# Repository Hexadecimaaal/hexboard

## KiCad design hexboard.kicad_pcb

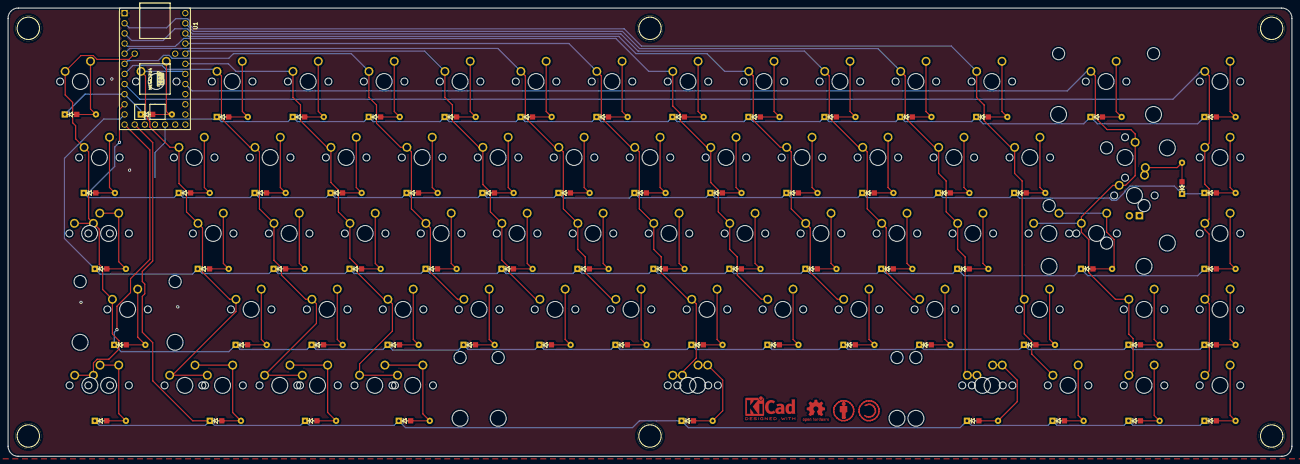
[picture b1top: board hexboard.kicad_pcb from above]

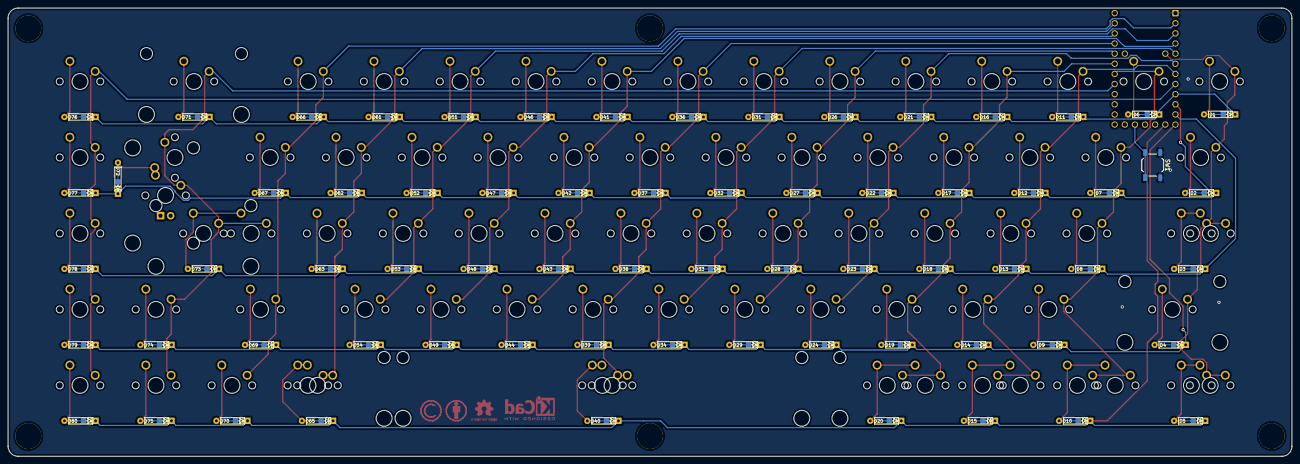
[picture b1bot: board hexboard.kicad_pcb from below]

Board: 2 copper layers, 321.9 x 112.4 mm, 151 parts (68 on the bottom side), 89 nets.

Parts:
D1, D2, D3, D4, D5, D6, D7, D8, D9, D10, D11, D12, D13, D14, D15, D16, D17, D18, D19, D20, D21, D22, D23, D24, D26, D27, D28, D29, D31, D32, D33, D34, D36, D37, D38, D39, D40, D41, D42, D43, D44, D46, D47, D48, D49, D51, D52, D53, D54, D61, D62, D63, D65, D66, D67, D69, D70, D71, D72, D73, D74, D75, D76, D77, D78, D79, D80: D_Small; Diode-hybrid-3pad
MX1, MX6, MX7, MX8, MX9, MX11, MX12, MX13, MX14, MX16, MX17, MX18, MX19, MX21, MX22, MX23, MX24, MX26, MX27, MX28, MX29, MX31, MX32, MX33, MX34, MX36, MX37, MX38, MX39, MX41, MX42, MX43, MX44, MX46, MX47, MX48, MX49, MX51, MX52, MX53, MX54, MX61, MX62, MX63, MX65ALT1, MX66, MX67, MX70, MX73ALT1, MX74, MX75, MX76, MX77, MX78, MX79, MX80: MX-NoLED; MXOnly-1U-NoLED
MX2: MX-NoLED; MXOnly-1.5U-NoLED
MX3, MX5, MX69: MX-NoLED; MXOnly-1.75U-NoLED
MX3ALT1, MX5ALT1, MX10, MX10ALT1, MX15, MX15ALT1, MX20, MX20ALT1, MX65: MX-NoLED; MXOnly-1.25U-NoLED
MX4, MX73: MX-NoLED; MXOnly-2.25U-NoLED
MX40: MX-NoLED; MXOnly-6.25U-NoLED
MX40ALT1: MX-NoLED; MXOnly-7U-NoLED
MX71: MX-NoLED; MXOnly-2U-NoLED
MX72: MX-NoLED; MXOnly-1.5U-Vertical-NoLED
MX72ALT1: MX-NoLED; MXOnly-ISO
SW1: SW_Push; SW_SPST_TL3342
U1: Teensy2.0_(C); Teensy2.0
U4, U4#2, U4#3, U4#4, U4#5, U4#6: HOLE; MountingHole

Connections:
/col1: MX1.1, MX2.1, MX3.1, MX3ALT1.1, MX4.1, MX5.1, MX5ALT1.1, U1.30
/col2: MX6.1, MX7.1, MX8.1, MX9.1, MX10.1, MX10ALT1.1, U1.23
/col3: MX11.1, MX12.1, MX13.1, MX14.1, MX15.1, MX15ALT1.1, U1.7
/col4: MX16.1, MX17.1, MX18.1, MX19.1, MX20.1, MX20ALT1.1, U1.24
/col5: MX21.1, MX22.1, MX23.1, MX24.1, U1.6
/col6: MX26.1, MX27.1, MX28.1, MX29.1, U1.25
/col7: MX31.1, MX32.1, MX33.1, MX34.1, U1.5
/col8: MX36.1, MX37.1, MX38.1, MX39.1, MX40.1, MX40ALT1.1, U1.26
/col9: MX41.1, MX42.1, MX43.1, MX44.1, U1.4
/col10: MX46.1, MX47.1, MX48.1, MX49.1, U1.27
/col11: MX51.1, MX52.1, MX53.1, MX54.1, U1.3
/col12: MX61.1, MX62.1, MX63.1, MX65.1, MX65ALT1.1, U1.28
/col13: MX66.1, MX67.1, MX69.1, MX70.1, U1.2
/col14: MX71.1, MX72.1, MX72ALT1.1, MX73.1, MX73ALT1.1, MX74.1, MX75.1, U1.22
/col15: MX76.1, MX77.1, MX78.1, MX79.1, MX80.1, U1.8
/row1: D1.1, D6.1, D11.1, D16.1, D21.1, D26.1, D31.1, D36.1, D41.1, D46.1, D51.1, D61.1, D66.1, D71.1, D76.1, U1.9
/row2: D2.1, D7.1, D12.1, D17.1, D22.1, D27.1, D32.1, D37.1, D42.1, D47.1, D52.1, D62.1, D67.1, D72.1, D77.1, U1.10
/row3: D3.1, D8.1, D13.1, D18.1, D23.1, D28.1, D33.1, D38.1, D43.1, D48.1, D53.1, D63.1, D73.1, D78.1, U1.11
/row4: D4.1, D9.1, D14.1, D19.1, D24.1, D29.1, D34.1, D39.1, D44.1, D49.1, D54.1, D69.1, D74.1, D79.1, U1.12
/row5: D5.1, D10.1, D15.1, D20.1, D40.1, D65.1, D70.1, D75.1, D80.1, U1.13
GND: SW1.1, U1.1
unnamed: D1.2, MX1.2
unnamed: D2.2, MX2.2
unnamed: D3.2, MX3.2, MX3ALT1.2
unnamed: D4.2, MX4.2
unnamed: D5.2, MX5.2, MX5ALT1.2
unnamed: D6.2, MX6.2
unnamed: D7.2, MX7.2
unnamed: D8.2, MX8.2
unnamed: D9.2, MX9.2
unnamed: D10.2, MX10.2, MX10ALT1.2
unnamed: D11.2, MX11.2
unnamed: D12.2, MX12.2
unnamed: D13.2, MX13.2
unnamed: D14.2, MX14.2
unnamed: D15.2, MX15.2, MX15ALT1.2
unnamed: D16.2, MX16.2
unnamed: D17.2, MX17.2
unnamed: D18.2, MX18.2
unnamed: D19.2, MX19.2
unnamed: D20.2, MX20.2, MX20ALT1.2
unnamed: D21.2, MX21.2
unnamed: D22.2, MX22.2
unnamed: D23.2, MX23.2
unnamed: D24.2, MX24.2
unnamed: D26.2, MX26.2
unnamed: D27.2, MX27.2
unnamed: D28.2, MX28.2
unnamed: D29.2, MX29.2
unnamed: D31.2, MX31.2
unnamed: D32.2, MX32.2
unnamed: D33.2, MX33.2
unnamed: D34.2, MX34.2
unnamed: D36.2, MX36.2
unnamed: D37.2, MX37.2
unnamed: D38.2, MX38.2
unnamed: D39.2, MX39.2
unnamed: D40.2, MX40.2, MX40ALT1.2
unnamed: D41.2, MX41.2
unnamed: D42.2, MX42.2
unnamed: D43.2, MX43.2
unnamed: D44.2, MX44.2
unnamed: D46.2, MX46.2
unnamed: D47.2, MX47.2
unnamed: D48.2, MX48.2
unnamed: D49.2, MX49.2
unnamed: D51.2, MX51.2
unnamed: D52.2, MX52.2
unnamed: D53.2, MX53.2
unnamed: D54.2, MX54.2
unnamed: D61.2, MX61.2
unnamed: D62.2, MX62.2
unnamed: D63.2, MX63.2
unnamed: D65.2, MX65.2, MX65ALT1.2
unnamed: D66.2, MX66.2
unnamed: D67.2, MX67.2
unnamed: D69.2, MX69.2
unnamed: D70.2, MX70.2
unnamed: D71.2, MX71.2
unnamed: D72.2, MX72.2, MX72ALT1.2
unnamed: D73.2, MX73.2, MX73ALT1.2
unnamed: D74.2, MX74.2
unnamed: D75.2, MX75.2
unnamed: D76.2, MX76.2
unnamed: D77.2, MX77.2
unnamed: D78.2, MX78.2
unnamed: D79.2, MX79.2
unnamed: D80.2, MX80.2
unnamed: SW1.2, U1.16

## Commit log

2020-06-29 first draft
2020-12-23 dunno whative changed whatever
2022-06-05 add iso footprints
